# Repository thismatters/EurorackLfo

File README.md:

# Low Frequency Oscillator

The Low Frequency Oscillator (LFO), as the name implies, oscillates at a low frequency. This implementation operates over a wide frequency range enabled by a rate knob and switch, offers access to 4 wave shapes simultaneously, and can be synced with an external clock.

The circuit here is based on the [Yusynth LFO 2](https://yusynth.net/Modular/EN/LFO/VC-LFO2.html) with minor tweaks to make it more Eurorack friendly. The changes I've made are thus:
* Selected resistors appropriate for +/-12V rails,
* Added polarity protection so that a backward power header doesn't fry anything (twin series schotty diodes: BAT54SL),
* Selected a modern dual NPN diode package for matched transistors,
* Full surface mount design.

The Yusynth page is a treasure trove of information about this circuit that I am too amateur to claim as my own; please read that outstanding page before using this circuit. The page provides many details and other implementations of this circuit that you may find suitable.

The KiCAD project here uses the library/footprints [found in my companion repo](https://github.com/thismatters/EurorackKiCAD).

## Width

6hp on a standard 3U rack.

## Inputs

Potentiometer labeled `rate` controls oscillation rate along with toggle switch to flip between `fast` and `slow`. Single `cv` input allows modulation of rate, which is augmented by a potentiometer labeled `cv`. Potentiometer labeled `pwm` adjusts the duty cycle for the square wave output. Oscillation can be synced to an external input by way of the `sync` input.

## Output

Four outputs, one for each of the following waveshapes: Sine, Saw, Triangle, Rectangle.
An LED visualizes the square wave output.

## Adjustment

You'll need an oscilloscope.

1. Set the `cv` knob to minimum.
1. Set the range switch to `slow`.
1. Set the `rate` knob to minimum.
1. Adjust RV4 until the LED blinks on every 10 seconds (0.1Hz)
1. Set the `rate` knob to maximum.
1. Connect the oscilloscope to the SAW output (sharp rising edge, ramp to low).
1. Adjust RV6 until the SAW output covers the -5V to 5V range.
1. Connect the oscilloscope to the TRIANGLE output.
1. Adjust RV7 until the TRIANGLE output covers the -5V to 5V range.
1. Connect the oscilloscope to the SINE output.
1. Adjust RV7 to perfect the SINE shape.
1. Set the range switch to `fast`.
1. Connect the oscilloscope to the TRIANGLE output.
1. Adjust RV5 to get a symmetric wave shape.

## Vendors

There are part numbers in the [BOM](lfo.csv) for many of the parts (not for basic passives though) at the following vendors:

* [Mouser](https://www.mouser.com): Needs no introduction. Get your ICs from here (or [digikey](https://www.digikey.com)).
* [Tayda Electronics](https://www.taydaelectronics.com/): Good supplier for passive components; audio jacks, and potentiometers. Their audio jacks are slightly smaller than the thonkiconn from thonk.
* [Love My Switches](https://lovemyswitches.com/): Has [really good knobs](https://lovemyswitches.com/anodized-aluminum-knob-the-lo-fi-1-4-smooth-shaft-12-5mm-od/) to go on those potentiometers!
* [OSHPark](https://oshpark.com/): Fast and (relatively) cheap PCB manufacturer. The [V0 circuit](https://oshpark.com/shared_projects/wfHu28zj) works well but has several bugs which are listed below.

# Bugs

## V0
* CV knob is backwards
* PWM knob is backwards
* Rate knob is backwards
* Kinda hard to dial in

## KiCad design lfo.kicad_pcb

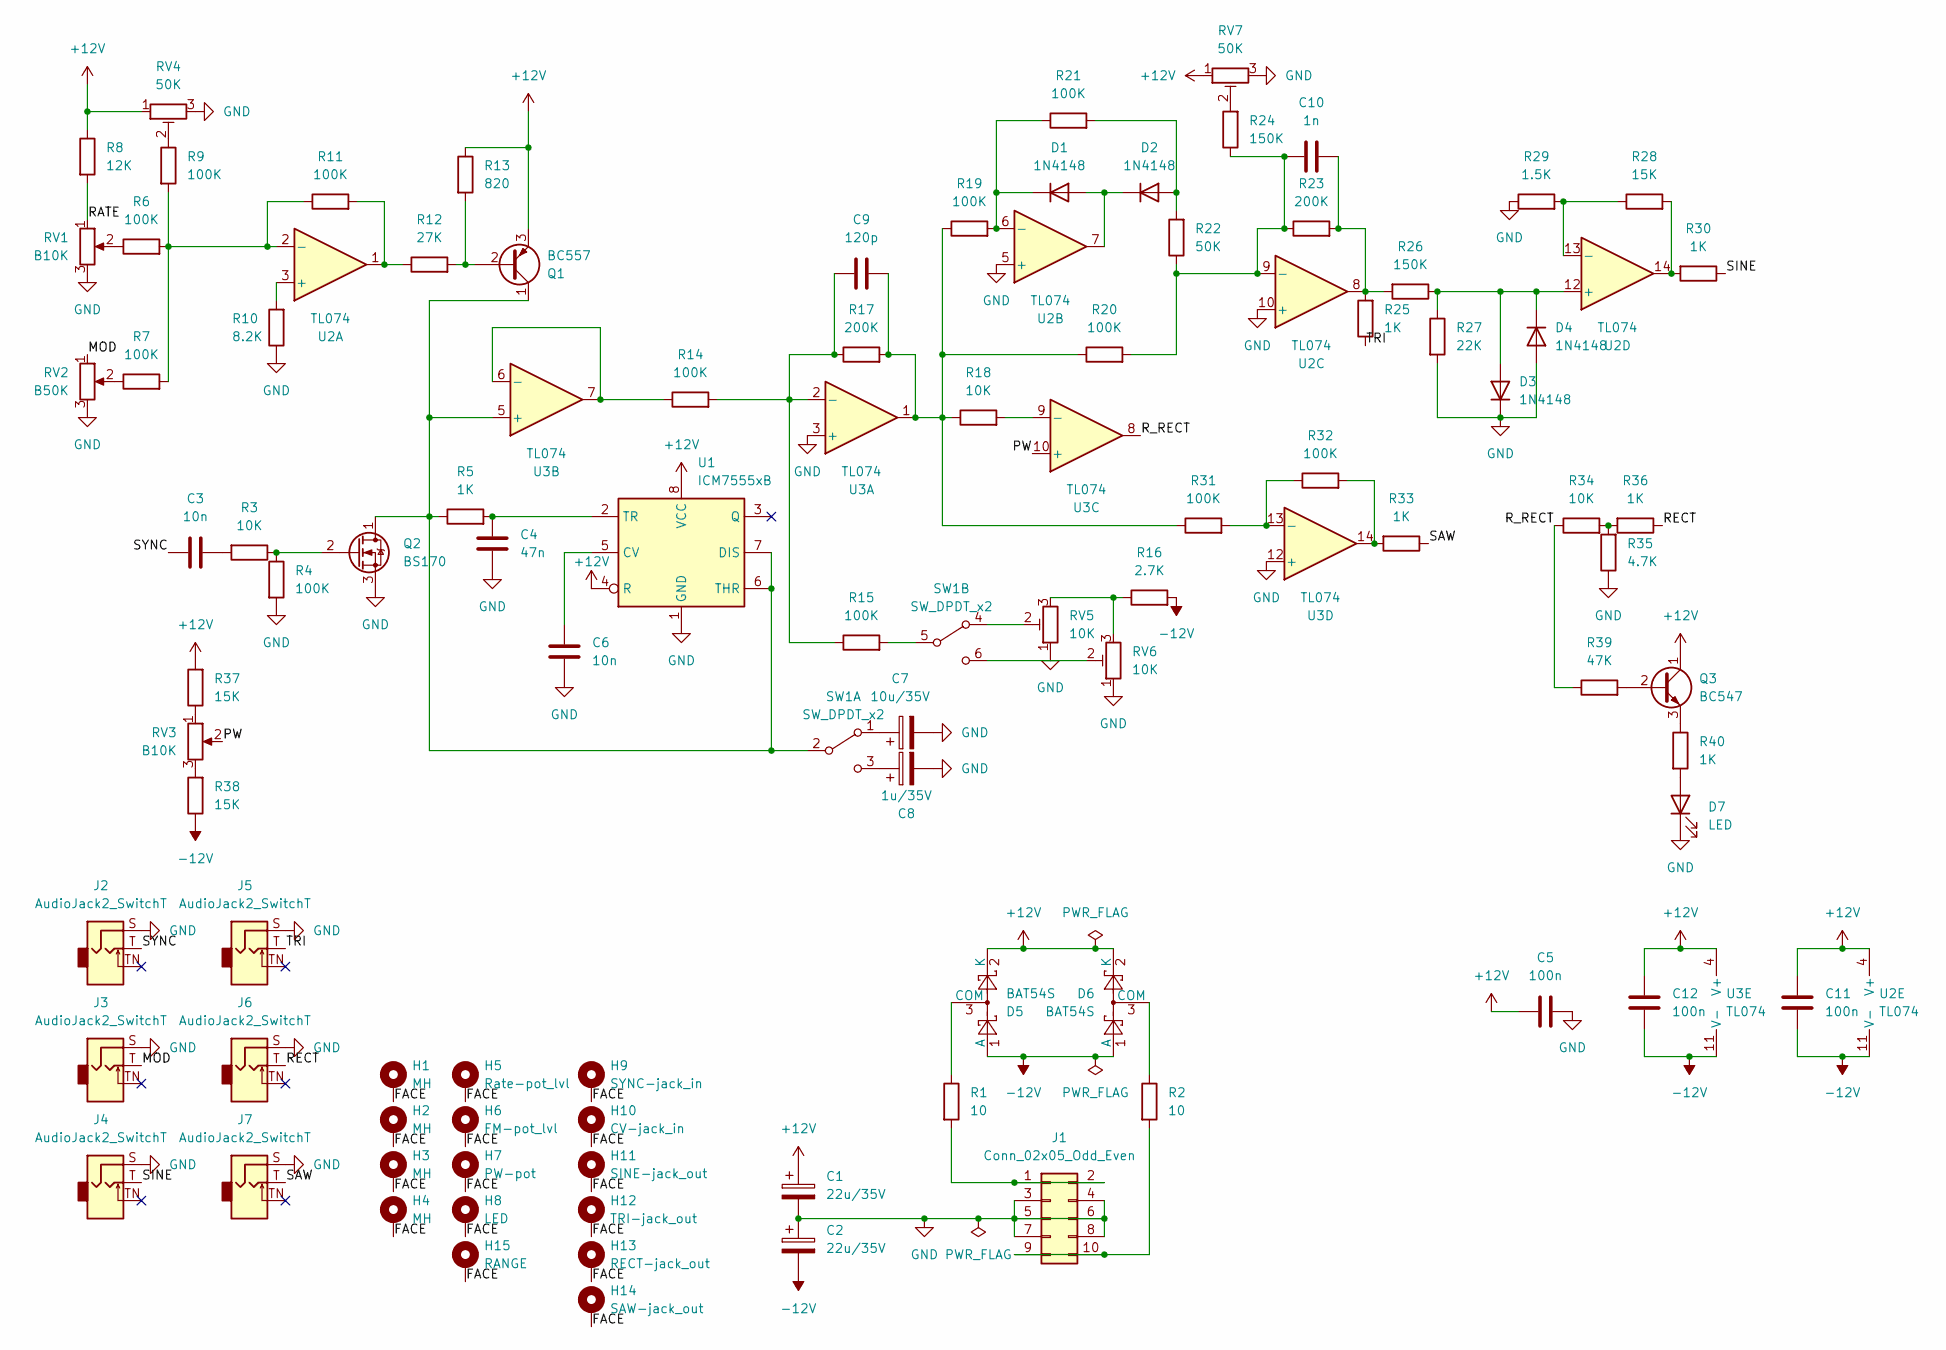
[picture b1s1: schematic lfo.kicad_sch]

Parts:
C1, C2: 22u/35V; CP_Radial_D5.0mm_P2.50mm
C3, C6: 10n; C_0805_2012Metric
C4: 47n; C_0805_2012Metric
C5, C11, C12: 100n; C_0805_2012Metric
C7: 10u/35V; CP_Radial_D5.0mm_P2.50mm
C8: 1u/35V; CP_Radial_D5.0mm_P2.50mm
C9: 120p; C_0603_1608Metric_Pad1.08x0.95mm_HandSolder
C10: 1n; C_0805_2012Metric
D1, D2, D3, D4: 1N4148; D_SOD-323_HandSoldering
D5, D6: BAT54S; SOT-23; PartNum 863-BAT54SLT1G
D7: LED; LED_D3.0mm
H1, H2, H3, H4: MH; Mech-MountingHole
H5: Rate-pot_lvl; Mech-Potentiometer-Hole_level
H6: FM-pot_lvl; Mech-Potentiometer-Hole_level
H7: PW-pot; Mech-Potentiometer-Hole_pan
H8: LED; Mech-LED-Hole-3mm-Bezel
H9: SYNC-jack_in; Mech-AudioJack-Hole
H10: CV-jack_in; Mech-AudioJack-Hole
H11: SINE-jack_out; Mech-AudioJack-Hole-Output
H12: TRI-jack_out; Mech-AudioJack-Hole-Output
H13: RECT-jack_out; Mech-AudioJack-Hole-Output
H14: SAW-jack_out; Mech-AudioJack-Hole-Output
H15: RANGE; Mech-2M_Switch-Hole
J1: Conn_02x05_Odd_Even; PinHeader_2x05_P2.54mm_Vertical; PartNum A-2939
J2, J3, J4, J5, J6, J7: AudioJack2_SwitchT; AudioJack2_Tayda_A-2566; PartNum A-2566
Q1: BC557; TO-92_Inline_Wide; PartNum 637-BC557B
Q2: BS170; TO-92_Inline_Wide; PartNum 512-BS170
Q3: BC547; TO-92_Inline_Wide; PartNum 637-BC547C
R1, R2: 10; R_0805_2012Metric
R3, R18, R34: 10K; R_0805_2012Metric
R4, R6, R7, R9, R11, R14, R15, R19, R20, R21, R31, R32: 100K; R_0805_2012Metric
R5, R25, R30, R33, R36, R40: 1K; R_0805_2012Metric
R8: 12K; R_0805_2012Metric
R10: 8.2K; R_0805_2012Metric
R12: 27K; R_0805_2012Metric
R13: 820; R_0805_2012Metric
R16: 2.7K; R_0805_2012Metric
R17, R23: 200K; R_0805_2012Metric
R22: 50K; R_0805_2012Metric
R24, R26: 150K; R_0805_2012Metric
R27: 22K; R_0805_2012Metric
R28, R37, R38: 15K; R_0805_2012Metric
R29: 1.5K; R_0805_2012Metric
R35: 4.7K; R_0805_2012Metric
R39: 47K; R_0805_2012Metric
RV1, RV3: B10K; Potentiometer_RV16AF-41-15R1; PartNum A-2969
RV2: B50K; Potentiometer_RV16AF-41-15R1; PartNum A-5401
RV4, RV7: 50K; Potentiometer_Bourns_3296W_Vertical
RV5, RV6: 10K; Potentiometer_Bourns_3296W_Vertical
SW1: SW_DPDT_x2; Switch_DPDT_Tayda_A-5752; PartNum A-6809
U1: ICM7555xB; SOIC-8_3.9x4.9mm_P1.27mm; PartNum 968-ICM7555CBAZ-T
U2, U3: TL074; SOIC-14_3.9x8.7mm_P1.27mm; PartNum 595-TL074CN

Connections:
+12V: C1.1, C5.1, C11.1, C12.1, D5.2 (K), D6.2 (K), Q1.3 (E), Q3.1 (C), R8.1, R13.1, R37.2, RV4.1, RV7.1, U1.4 (R), U1.8 (VCC), U2.4 (V+), U3.4 (V+)
-12V: C2.2, C11.2, C12.2, D5.1 (A), D6.1 (A), R16.2, R38.1, U2.11 (V-), U3.11 (V-)
/FACE: H1.1, H2.1, H3.1, H4.1, H5.1, H6.1, H7.1, H8.1, H9.1, H10.1, H11.1, H12.1, H13.1, H14.1, H15.1
/MOD: J3.T, RV2.1
/PW: RV3.2, U3.10 (+)
/RATE: R8.2, RV1.1
/RECT: J6.T, R36.1
/R_RECT: R34.1, R39.1, U3.8
/SAW: J7.T, R33.1
/SINE: J4.T, R30.1
/SYNC: C3.1, J2.T
/TRI: J5.T, R25.1
GND: C1.2, C2.1, C4.1, C5.2, C6.2, C7.2, C8.2, D3.1 (K), D4.2 (A), D7.1 (K), J1.3, J1.4, J1.5, J1.6, J1.7, J1.8, J2.S, J3.S, J4.S, J5.S, J6.S, J7.S, Q2.3 (S), R4.2, R10.1, R27.2, R29.1, R35.1, RV1.3, RV2.3, RV4.3, RV5.1, RV6.1, RV7.3, U1.1 (GND), U2.5 (+), U2.10 (+), U3.3 (+), U3.12 (+)
unnamed: C3.2, R3.2
unnamed: C9.2, R17.2, R18.1, R19.1, R20.1, R31.1, U3.1
unnamed: C10.2, R23.2, R25.2, R26.2, U2.8
unnamed: D1.2 (A), D2.1 (K), U2.7
unnamed: D1.1 (K), R19.2, R21.1, U2.6 (-)
unnamed: D2.2 (A), R21.2, R22.2
unnamed: D3.2 (A), D4.1 (K), R26.1, R27.1, U2.12 (+)
unnamed: D5.3 (COM), R1.1
unnamed: D6.3 (COM), R2.1
unnamed: D7.2 (A), R40.2
unnamed: J1.1, J1.2, R1.2
unnamed: J1.9, J1.10, R2.2
unnamed: Q1.2 (B), R12.2, R13.2
unnamed: Q1.1 (C), Q2.1 (D), R5.1, SW1.2 (B), U1.6 (THR), U1.7 (DIS), U3.5 (+)
unnamed: Q2.2 (G), R3.1, R4.1
unnamed: Q3.2 (B), R39.2
unnamed: Q3.3 (E), R40.1
unnamed: R6.1, RV1.2
unnamed: R7.1, RV2.2
unnamed: R9.1, RV4.2
unnamed: R11.2, R12.1, U2.1
unnamed: R16.1, RV5.3, RV6.3
unnamed: R24.2, RV7.2
unnamed: R28.2, R30.2, U2.14
unnamed: R32.2, R33.2, U3.14
unnamed: R34.2, R35.2, R36.2
unnamed: R37.1, RV3.1
unnamed: R38.2, RV3.3
unnamed: C7.1, SW1.1 (A)
unnamed: C8.1, SW1.3 (C)
unnamed: RV5.2, SW1.4 (A)
unnamed: R15.2, SW1.5 (B)
unnamed: RV6.2, SW1.6 (C)
unnamed: C6.1, U1.5 (CV)
unnamed: C4.2, R5.2, U1.2 (TR)
unnamed: R10.2, U2.3 (+)
unnamed: R6.2, R7.2, R9.2, R11.1, U2.2 (-)
unnamed: C10.1, R20.2, R22.1, R23.1, R24.1, U2.9 (-)
unnamed: R28.1, R29.2, U2.13 (-)
unnamed: C9.1, R14.2, R15.1, R17.1, U3.2 (-)
unnamed: R14.1, U3.6 (-), U3.7
unnamed: R18.2, U3.9 (-)
unnamed: R31.2, R32.1, U3.13 (-)

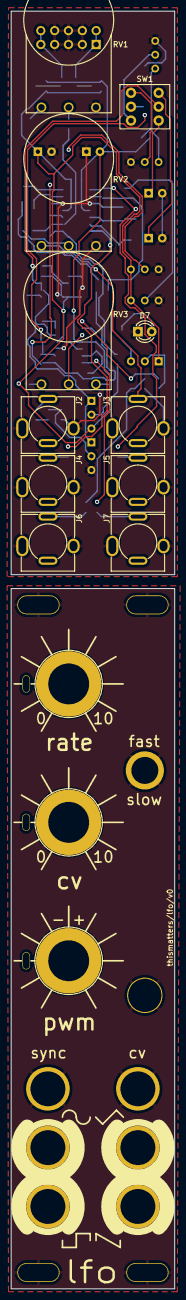
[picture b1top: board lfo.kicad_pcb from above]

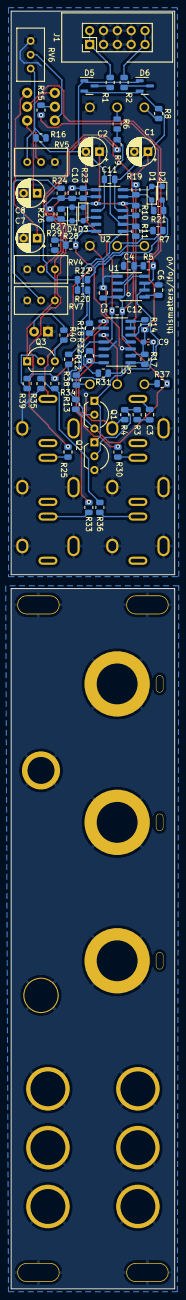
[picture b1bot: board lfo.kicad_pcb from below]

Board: 2 copper layers, 30.0 x 234.4 mm, 95 parts (69 on the bottom side), 56 nets.

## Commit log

2024-04-25 updating bom
2024-04-25 fix pcb
2024-11-24 annotating some issues
